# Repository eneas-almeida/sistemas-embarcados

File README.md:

# Sistemas Embarcados - 2021.2

## 1. Instituição

-   Instituto Federal da Paraíba - IFPB
-   Campus Campina Grande

## 2. Docente responsável

-   [Professor Dr. Alexandre Sales Vasconcelos](https://github.com/alexandresvifpb)

## 3. Grupo

-   [Edivam Enéas de Almeida Júnior](https://github.com/venzel)
-   [Erickson Tulio Rodrigues Azevêdo](https://github.com/Erickson-Eng)
-   [Joab da Silva Maia](https://github.com/JoabMaia)

## 4. Descrição do projeto

Nesse projeto foi realizado desenvolvimento de um sistema embarcado que é capaz de identificar vazamento de gases, além disso, também apresenta todas as informações desse vazamento a partir de um display led e faz envio de mensagens SMS para celulares cadastrados em uma aplicação integrada.

## 5. Objetivos

### 5.1. Geral

-   O objetivo geral deste trabalho é o desenvolvimento de uma hardware de segurança doméstica para fornecer um sinal de alarme ao usuário caso aconteça vazamento de gás, além de informações na tela de temperatura.

### 5.2. Específicos

-   Criar um prototipo que seja capaz de realizar detecção de gás, apresentação de resultados via display e também conseguir realizar envio de mensagens SMS para o dispositivo cadastrado.

## 6. Resumo das arquiteturas

A seguir é no tópico 1 _Hardware_ é apresentado a placa e o case ambos construídos no aplicativo fusion 360 e em seguida no tópico 2 _Firmaware e/ou Software/App_ é apresentado as especificações como circuito eletrico e PCB.

### 6.1. Desenhos

-   3D

-   PCB

-   Circuito elétrico

## 7. Firmwares

👉 [Teste do display lcd com I2C](./firmwares/teste_lcd_I2C/teste_lcd_I2C.ino)<br />
👉 [Teste do sensor de temperatura](./firmwares/teste_sensor_temperatura/teste_sensor_temperatura.ino)<br />
👉 [Teste do sensor de gás](./firmwares/teste_sensor-gas/teste_sensor-gas.ino)<br />
👉 [Teste da conexão com o wifi](./firmwares/teste_wifi/teste_wifi.ino)<br />
👉 [Código do projeto (v1)](./firmwares/codigo_final_projeto/codigo_final_projeto.ino)<br />
👉 [Código do projeto (v2)](./firmwares/projeto)

## 8. Vídeo do protótipo

## 9. Vídeo da apresentação

## 10. Diagrama de processo

## 11. Diagrama de bloco

## 12. Resumo dos Resultados

Nesse projeto foi possível construir um protótipo capaz de realizar a detecção de gases inflamáveis, além disso, através do sistema é possível disparar alertas tanto para sua própria interface que é um componente LCD de 16 colunas e duas linhas, um alto-falante para emitir sinais sonoros e por fim interfaces externas com o uso de mensagem via SMS.

<div align="center"></div>

Outro recurso importante que também implementado foi a integração do sistema com uma api de envio de SMS, o **IFTT**, onde é possível através de uma chamada JSON, se comunicar com o serviço e efetuar disparos de SMS.

**Foi possível atingir os seguintes objetivos adicionais:**

-   Implementar sistema de interrupções.
-   Instalação de libs dos módulos.
-   Realizar a implementação de threads.

👉 [Relatório final do projeto (PDF)](./results/relatorio-final.pdf)<br />

## 13. Link dos arquivos

👉 [Esquema elétrico (EAGLE)](./3d/projeto_dispositivo_alarme_gas/esquema_eletrico/esquema_eletrico_eagle.sch)<br />
👉 [Esquema elétrico (FUSION)](./3d/projeto_dispositivo_alarme_gas/esquema_eletrico/esquema_eletrico_fusion.fsch)<br />
👉 [Imagens com furos da PCB (PARTE INFERIOR)](./3d/projeto_dispositivo_alarme_gas/imagem_bottom_side_da_pcb_manufacturing/imagem_bottom_side_da_pcb_manufacturing.png)<br />
👉 [Imagens com furos da PCB (PARTE SUPERIOR)](./3d/projeto_dispositivo_alarme_gas/imagem_top_side_da_pcb_manufacturing/imagem_top_side_da_pcb_manufacturing.png)<br />
👉 [Medidas dos furos da PCB (1)](./3d/projeto_dispositivo_alarme_gas/imagem_drils_da_pcb/imagem_drils_da_pcb.png)<br />
👉 [Medidas dos furos da PCB (2)](./3d/projeto_dispositivo_alarme_gas/imagem_drils_da_pcb/metricas_drills.csv)<br />
👉 [Layout da PCB (EAGLE)](./3d/projeto_dispositivo_alarme_gas/layout_da_pcb/layout_da_pcb_eagle.brd)<br />
👉 [Layout da PCB (FUSION)](./3d/projeto_dispositivo_alarme_gas/layout_da_pcb/layout_da_pcb_fusion.fbrd)<br />
👉 [Desenho 3D - Apenas PCB (FUSION)](./3d/projeto_dispositivo_alarme_gas/modelo_3d_da_pcb/modelo_3d_da_pcb.f3d)<br />
👉 [Desenho 3D - PCB + CASE (FUSION)](./3d/projeto_dispositivo_alarme_gas/modelo_3d_da_pcb/modelo_3d_da_pcb_e_case.f3z)

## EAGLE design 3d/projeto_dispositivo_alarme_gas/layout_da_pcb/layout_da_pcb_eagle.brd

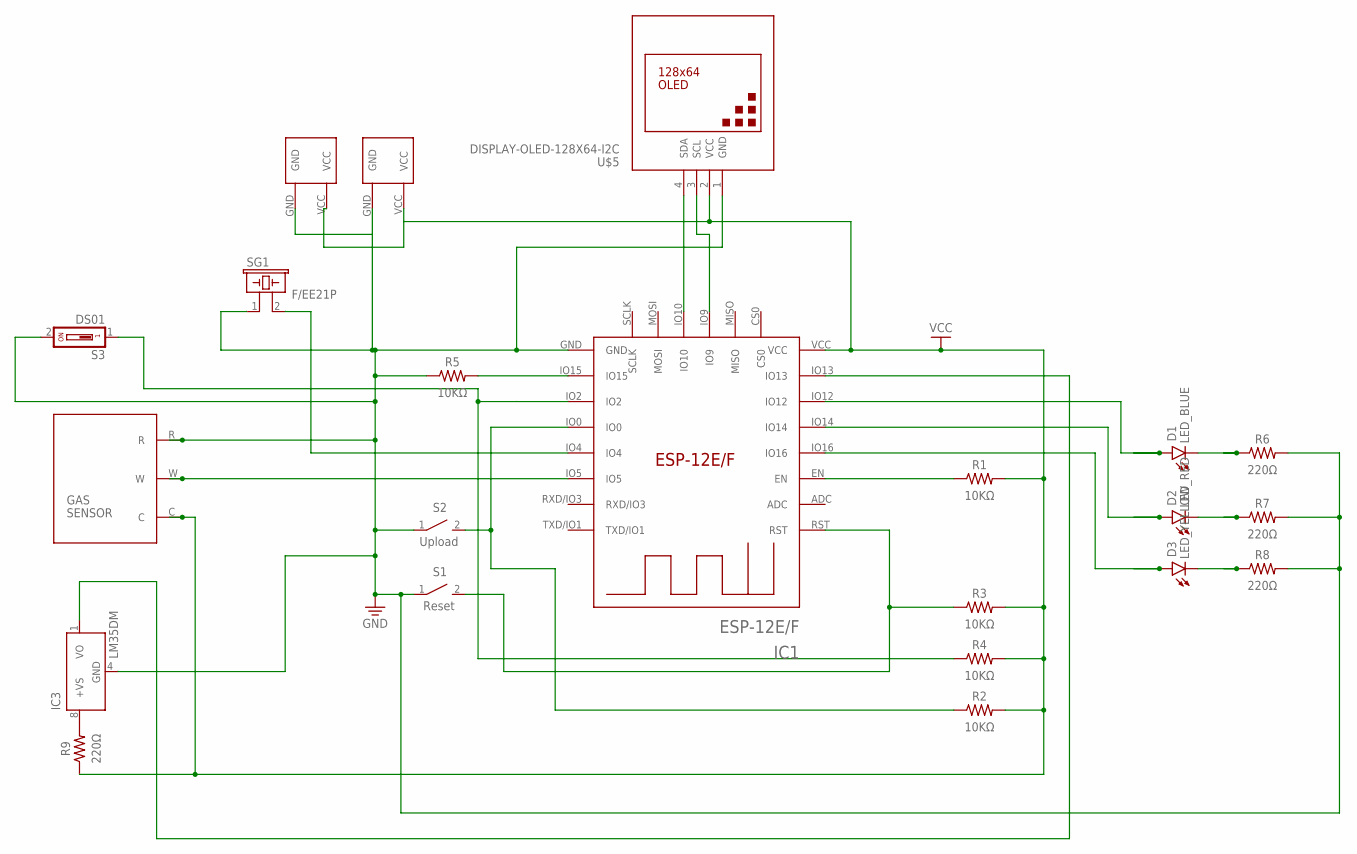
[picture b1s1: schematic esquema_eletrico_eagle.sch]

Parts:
D1: LED_BLUE; LEDRD254W60D565H860B_B
D2: LED_RED; LEDRD254W60D565H860B
D3: LED_YELLOW; LEDRD254W60D565H860B_Y
IC1: ESP-12E/F; ESP-12E
IC3: LM35DM; SO08
R1, R2, R3, R4, R5: 10KΩ; RESAD724W46L381D178B
R6, R7, R8, R9: 220Ω; RESAD724W46L381D178B
S1: Reset; B3U-1000P(M)-B
S2: Upload; B3U-1000P(M)-B
S3: DS01; DS-01
SG1: F/EE21P
U$1, U$3: CR2032; CR2032-20MM
U$2: 3-ELECTRODE-GAS-SENSOR; 3-ELECTRODE
U$5: DISPLAY-OLED-128X64-I2C

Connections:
GND: IC1.GND, IC3.4 (GND), R5.1, R6.2, R7.2, R8.2, S1.1, S2.1, S3.2, SG1.1, U$1.GND, U$2.R, U$3.GND, U$5.1 (GND)
unnamed: IC1.RST, R3.1, S1.2
unnamed: IC1.IO15, R5.2
unnamed: IC1.EN, R1.1
unnamed: IC1.IO2, R4.1, S3.1
unnamed: IC1.IO0, R2.1, S2.2
unnamed: IC1.IO4, SG1.2
unnamed: IC1.IO5, U$2.W
unnamed: IC1.IO13, IC3.1 (VO)
unnamed: D1.1 (A), IC1.IO12
unnamed: D2.1 (A), IC1.IO14
unnamed: D3.1 (A), IC1.IO16
unnamed: D1.2 (C), R6.1
unnamed: D2.2 (C), R7.1
unnamed: D3.2 (C), R8.1
unnamed: IC3.8 (+VS), R9.2
unnamed: IC1.IO10, U$5.4 (SDA)
unnamed: IC1.IO9, U$5.3 (SCL)
VCC: IC1.VCC, R1.2, R2.2, R3.2, R4.2, R9.1, U$1.VCC, U$2.C, U$3.VCC, U$5.2 (VCC)

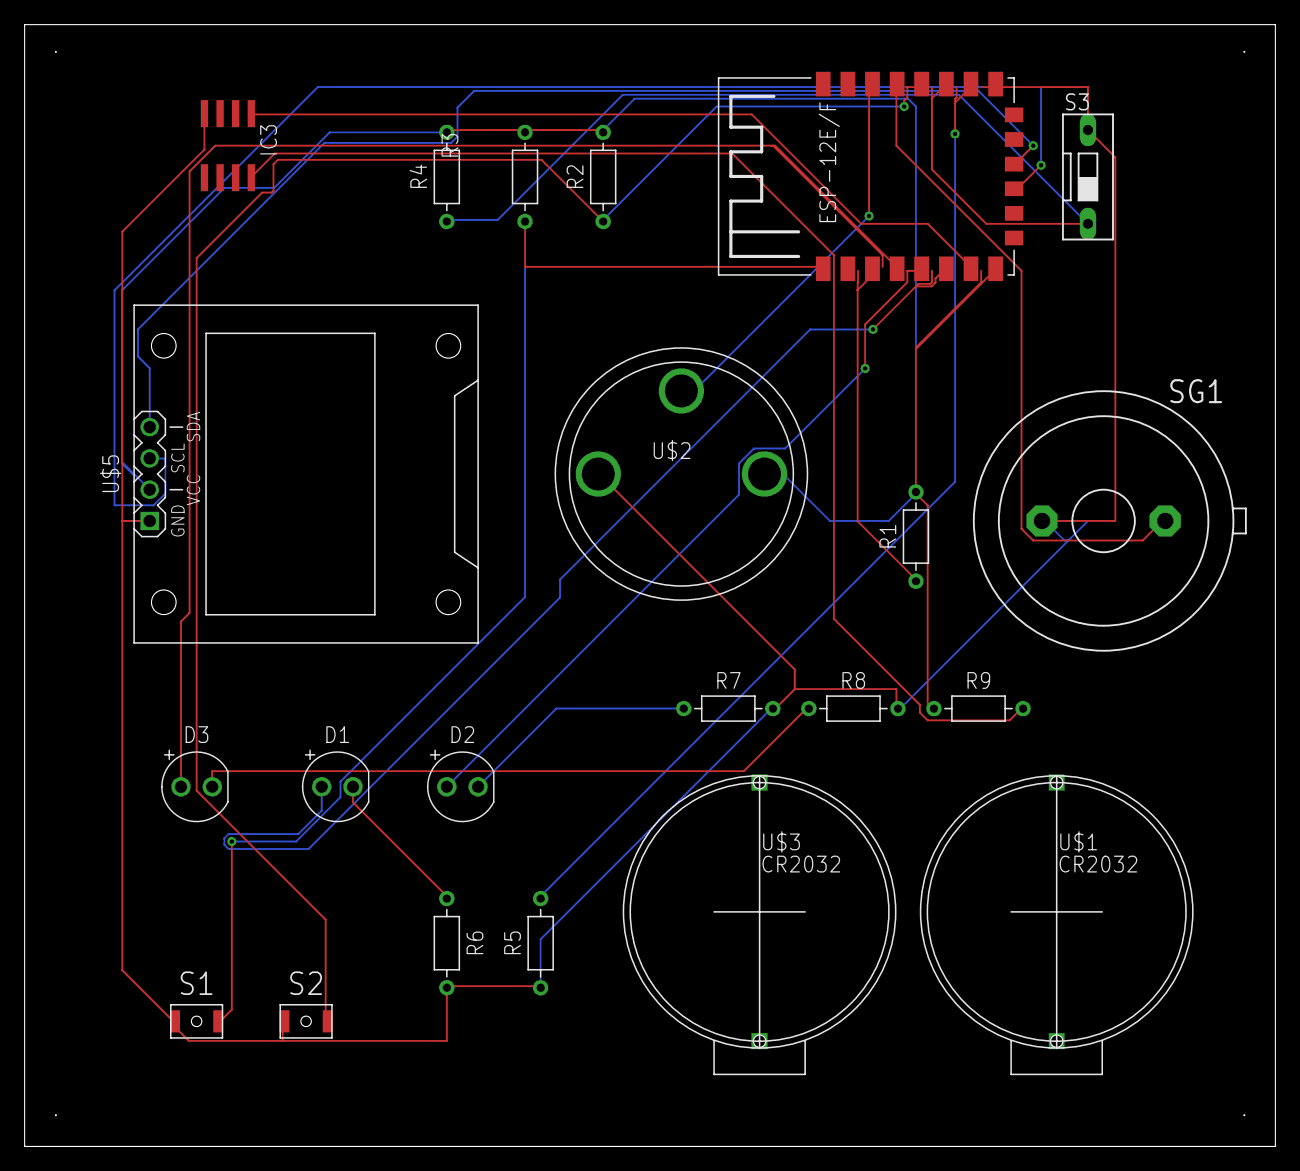
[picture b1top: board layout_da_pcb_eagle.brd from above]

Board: 2 copper layers, 101.6 x 91.1 mm, 22 parts (0 on the bottom side), 19 nets.

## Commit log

2022-03-10 colocado o readme no padrão e inserido uma pasta onde deverá ficar todos os arquivos estaticos
2022-03-10 inserido imagem do hardware
2022-03-10 Firmware
2022-03-10 inclusão das imagens na aba firmware
2022-03-10 inclusão de objetivo geral e especifico
2022-03-10 descrição do projeto
2022-03-13 readme update
2022-03-13 mudança na estrutura de diretorios
2022-03-13 mudanca na estrutura de arquivos
2022-03-13 imagens com link quebrado no readme
2022-03-13 imagens com link quebrado
2022-03-18 docs: modifica documentacao
2022-03-18 docs: modifica documentacao v2
2022-03-18 docs: modifica documentacao v3
2022-03-19 docs: modifica documentacao v4
2022-03-19 docs: modifica documentacao v5
2022-03-19 docs: modifica documentacao v6
2022-03-19 docs: modifica documentacao v7
2022-03-19 docs: modifica documentacao v8
2022-03-19 docs: modifica documentacao v9
2022-03-19 docs: modifica documentacao v10
2022-03-19 docs: modifica documentacao v11
2022-03-19 docs: modifica documentacao v12
2022-03-19 docs: modifica documentacao v13
2022-03-19 docs: modifica documentacao v14
2022-03-19 docs: modifica documentacao v15
2022-03-19 docs: modifica documentacao v17
2022-03-19 docs: modifica documentacao v18
2022-03-19 docs: modifica documentacao v19
2022-03-19 Create LICENSE
2022-03-19 docs: altera a readme v20
2022-03-19 docs: altera a readme v21
2022-03-19 docs: altera a readme v22
2022-03-19 docs: altera a readme v23
2022-03-19 video final
2022-03-19 docs: altera a readme v24
2022-03-20 docs: altera a readme v25
2022-03-20 docs: altera a readme v26

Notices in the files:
parts and their libraries:
oled: Released under the Creative Commons Attribution 4.0 International License: http://creativecommons.org/licenses/by/4.0
